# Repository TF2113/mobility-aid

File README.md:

<h1 align="center">Huia Echo 🐸</h1>

# 👁️‍🗨️ Mobility Aid for Visually Impaired Users

A low-cost embedded system designed to assist visually impaired individuals using real-time **proximity sensing** and **traffic light recognition**. Built on a Raspberry Pi, the system integrates ultrasonic sensors, a camera, and a lightweight machine learning model (YOLOv11n) to detect environmental conditions and provide haptic feedback.

---

## 📌 Overview

This mobility aid project helps users safely navigate streets, particularly at pedestrian crossings. The system combines:

- **Ultrasonic sensing** to detect nearby obstacles
- **Traffic light recognition** using a camera and an efficient YOLOv11n model
- **Feedback mechanism** via vibration, triggered based on proximity and light state

---

## 📁 Key File Structure

```
mobility-aid/
│
├── include/                  # C header files
│   ├── config_loader.h       # Loads external config values
│   ├── gpio_functions.h      # GPIO pin setup and control
│   └── tick.h                # Timing utilities
│
├── src/                      # C source files
│   ├── configs/              # Config database using data generated by web app
│   │   └── config.db
│   └── sys_controller.c      # Ultrasonic sensor and control loop                         
│
├── ml/                       # Machine learning module
│   ├── augmentation.ipynb    # Data augmentation and preprocessing
│   ├── train_model.ipynb     # YOLOv11n training logic
│   └── models/
│       └── best.pt           # Trained YOLOv11n model weights
│
├── test/                     # Test cases, mocks and framework files for testing C & Python
│
├── web/                      # Web interface (Flask app)
│   └── app.py                # Local dashboard
│
├── Makefile                  # Compiles the C code
├── .gitignore
├── start.py                  # Orchestrates all components (C binary, ML, server)    
├── requirements.txt
└── README.md                 
```

---

## 🚀 Features

- 📡 **Ultrasonic Sensing**  
  Detects objects and measures distance with HC-SR04 sensor.

- 🧠 **Traffic Light Recognition (YOLOv11n)**  
  Recognizes red/green pedestrian and traffic lights from a camera feed.

- 🔊 **Feedback System**  
  Triggers vibration when objects are too close or crossing is unsafe.

- ⚙️ **Modular Design**  
  Split into embedded C for performance and Python for AI tasks.

- 🪛 **Easily Configurable**  
  Adjust logic thresholds via external config files.

---

## 🧠 Machine Learning

- **Model:** YOLOv11n (Ultralytics)
- **Dataset:** Custom images gathered and augmented to increase dataset size
- **Use Case:** Detect green/red pedestrian signals in real time
- **Output:** Torch `.pt` model located at `ml/models/best.pt`
- **Trained Using:**  
  - `augmentation.ipynb`: Image resizing, color shifts, flips  
  - `train_model.ipynb`: Fine-tuning YOLOv11n with labeled traffic light data

## 🖥️ Requirements

### Hardware

- Raspberry Pi 4 (or newer)
- HC-SR04 Ultrasonic sensor
- Pi Camera Module
- Vibration motor or buzzer

---

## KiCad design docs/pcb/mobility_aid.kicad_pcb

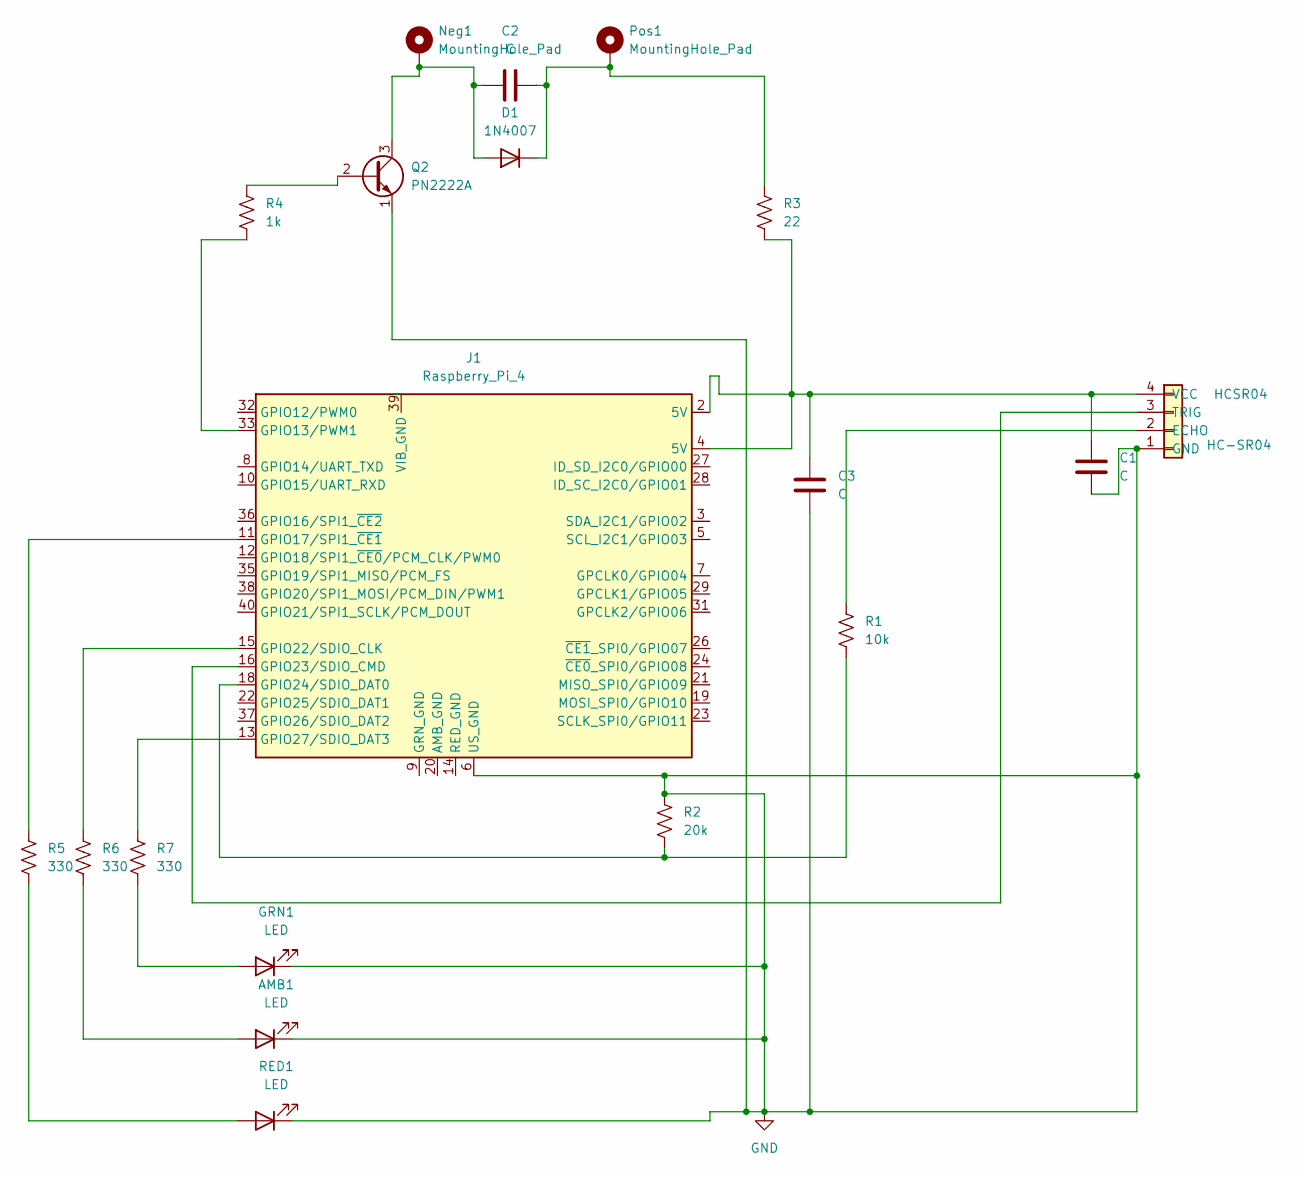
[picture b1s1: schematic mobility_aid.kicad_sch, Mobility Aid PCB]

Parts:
AMB1: LED; LED_D5.0mm
C1, C2: C; C_Disc_D5.0mm_W2.5mm_P2.50mm
C3: C; CP_Radial_D6.3mm_P2.50mm
D1: 1N4007; D_DO-41_SOD81_P10.16mm_Horizontal
GRN1: LED; LED_D5.0mm
HCSR04: HC-SR04; PinSocket_1x04_P2.54mm_Horizontal
J1: Raspberry_Pi_4; PinSocket_2x20_P2.54mm_Vertical
Neg1: MountingHole_Pad; MountingHole_2.5mm_Pad
Pos1: MountingHole_Pad; MountingHole_2.5mm_Pad
Q2: PN2222A; TO-92_Inline
R1: 10k; R_Axial_DIN0207_L6.3mm_D2.5mm_P7.62mm_Horizontal
R2: 20k; R_Axial_DIN0207_L6.3mm_D2.5mm_P7.62mm_Horizontal
R3: 22; R_Axial_DIN0207_L6.3mm_D2.5mm_P7.62mm_Horizontal
R4: 1k; R_Axial_DIN0207_L6.3mm_D2.5mm_P7.62mm_Horizontal
R5, R6, R7: 330; R_Axial_DIN0207_L6.3mm_D2.5mm_P7.62mm_Horizontal
RED1: LED; LED_D5.0mm

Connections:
GND: AMB1.1 (K), C1.2, C3.2, GRN1.1 (K), HCSR04.1 (GND), J1.6 (US_GND), J1.9 (GND), J1.14 (GND), J1.20 (GND), J1.25 (GND), J1.30 (GND), J1.34 (GND), J1.39 (GND), Q2.1 (E), R2.1, RED1.1 (K)
unnamed: AMB1.2 (A), R6.2
unnamed: C2.1, D1.2 (A), Neg1.1, Q2.3 (C)
unnamed: C2.2, D1.1 (K), Pos1.1, R3.1
unnamed: GRN1.2 (A), R7.2
unnamed: HCSR04.2 (ECHO), R1.1
unnamed: HCSR04.3 (TRIG), J1.16 (GPIO23/SDIO_CMD)
unnamed: C1.1, C3.1, HCSR04.4 (VCC), J1.2 (5V), J1.4 (5V), R3.2
unnamed: J1.33 (GPIO13/PWM1), R4.2
unnamed: J1.11 (GPIO17/SPI1_~CE1), R5.1
unnamed: J1.15 (GPIO22/SDIO_CLK), R6.1
unnamed: J1.18 (GPIO24/SDIO_DAT0), R1.2, R2.2
unnamed: J1.13 (GPIO27/SDIO_DAT3), R7.1
unnamed: Q2.2 (B), R4.1
unnamed: R5.2, RED1.2 (A)

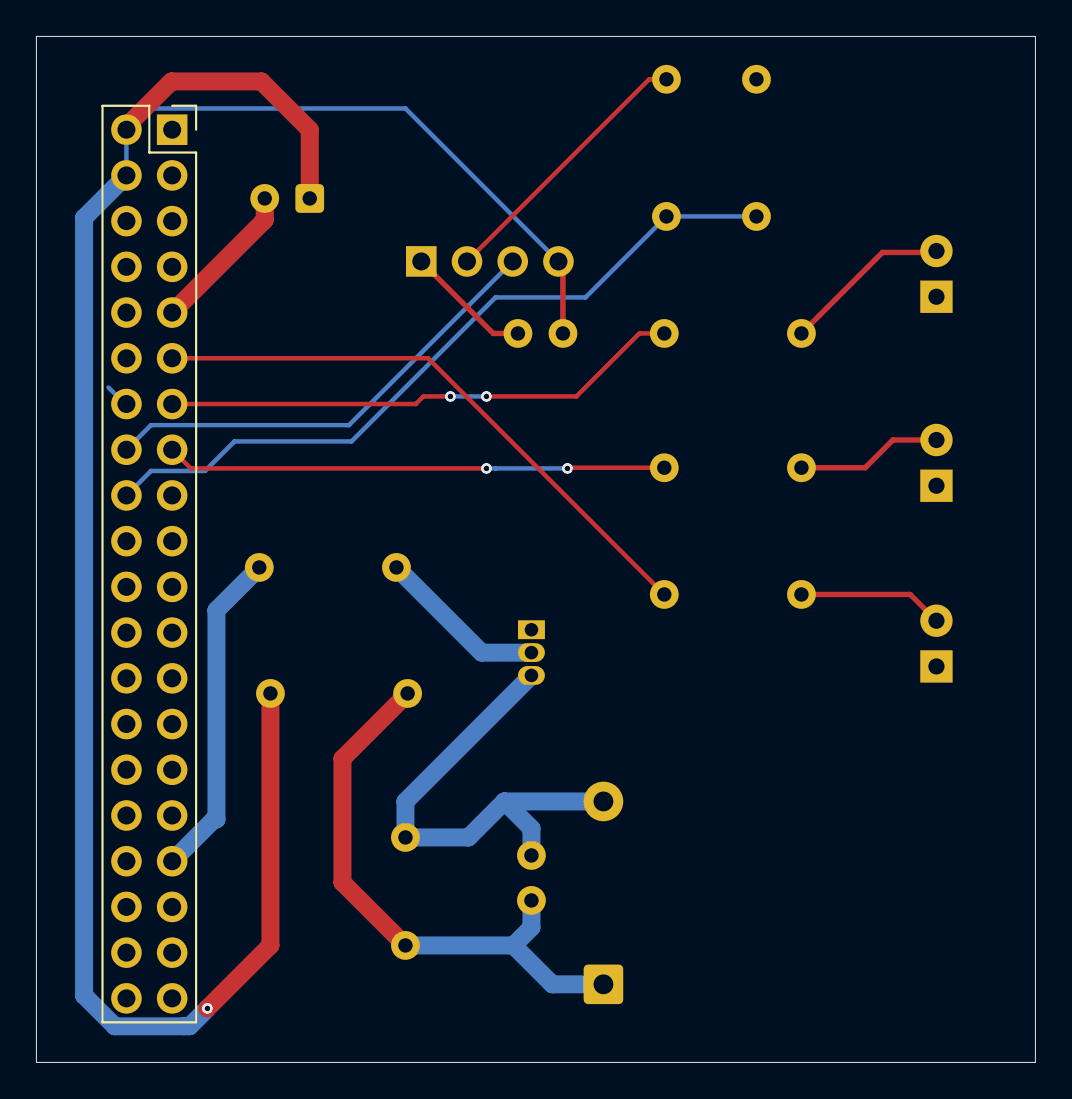
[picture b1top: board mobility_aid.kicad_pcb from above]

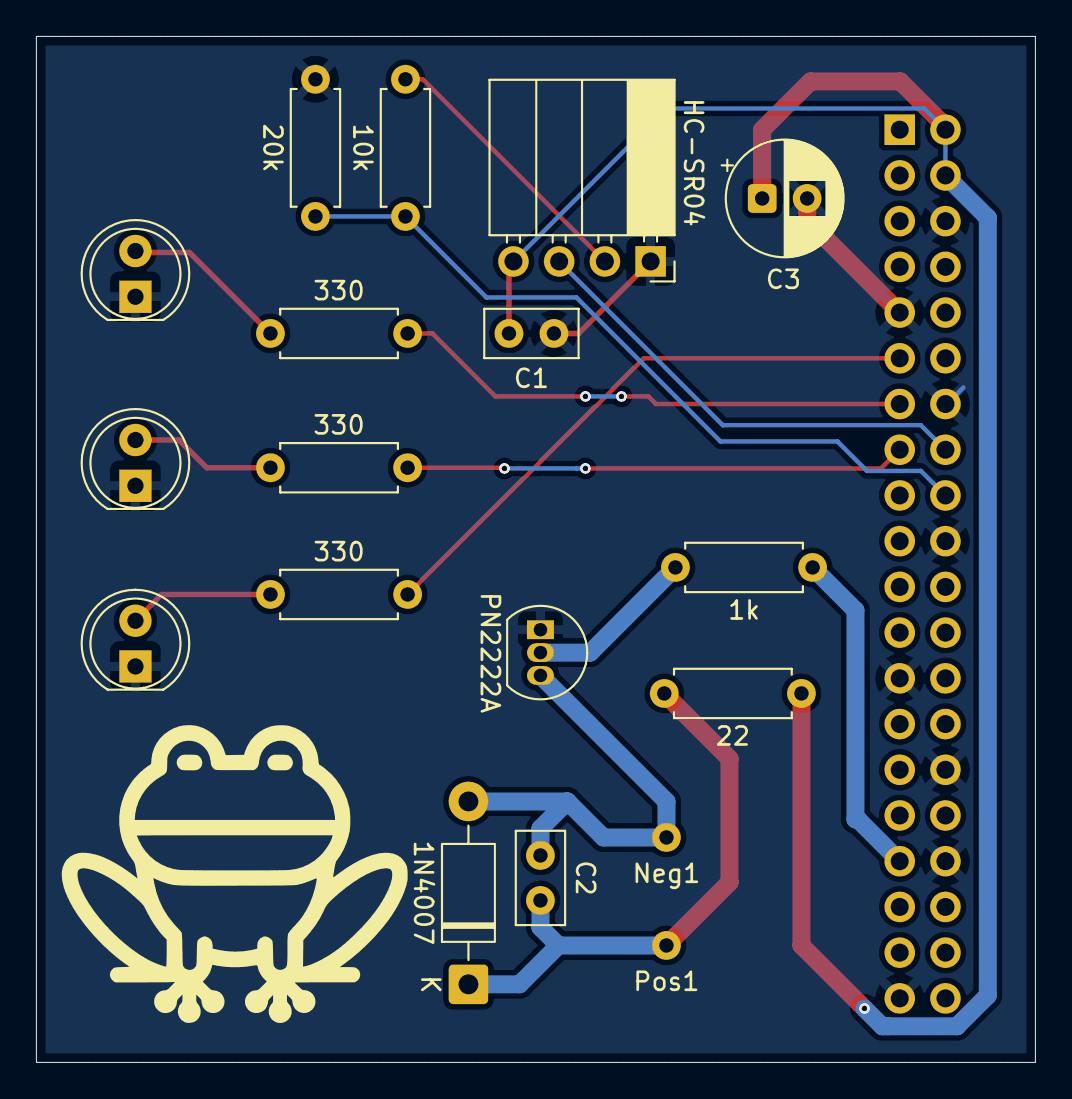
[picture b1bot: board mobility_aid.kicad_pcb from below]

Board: 2 copper layers, 55.5 x 57.0 mm, 19 parts (18 on the bottom side), 15 nets.

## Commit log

2025-06-09 Add initial implementation of GPIO memory access
2025-06-09 Initialize GPIO registers for TRIG, ECHO, and LED in proximity sensor setup
2025-06-09 Add getTick utility functions and update .vscode configuration files
2025-06-09 Update C/C++ configuration for ARM64 support and clean up include paths
2025-06-10 Rename header and struct to avoid <time.h> conflicts, implement distance sensing with LED response
2025-06-10 Add further comments to clarify code
2025-06-10 Compile basic program
2025-06-10 Add Makefile for compiling to /builds, remove git tracking for /builds
2025-06-10 Update comments
2025-06-10 Add green power indicator LED that is on while program is running
2025-06-10 Add loop to blink LED when proximity detected and print distance measured
2025-06-10 Add distance-based blinking frequency for LED
2025-06-11 Create C++ program to capture image from R Pi Camera
2025-06-11 Fix indentation
2025-06-11 Update Makefile to include both current programs
2025-06-13 Add yellow LED for intermediate distance added, refactor GPSEL2 logic to modify all related GPIO at once, code formatted
2025-06-13 Fix commit error
2025-06-13 Remove delay after red GPCLR for faster feedback before next reading
2025-06-16 Add GPIO functions to external .c file to improve modularity
2025-06-16 Refactor prox_sensor to use new GPIO functions module, fix syntax bug in gpioLevel0 function
2025-06-16 Remove redundant definitions
2025-06-16 Move datasheet link from prox_sensor to gpio_functions.c
2025-06-19 Create first iteration of image augmentation pipeline using Albumentations
2025-06-19 Remove image zip output
2025-06-20 Move augmentations.ipynb to ML folder
2025-06-20 Move ML folder out of src folder
2025-06-20 Remove unused import
2025-07-02 Create intial model training notebook
2025-07-02 Update output file structure to work better for training
2025-07-02 Add classes.txt file to output zip
2025-07-02 Add augmentation zip file output handling
2025-07-02 Add ML training command to allow for test trainings
2025-07-03 Add vibration feedback functionality for object proximity
2025-07-03 Update previous comments to reflect new logic
2025-07-10 Add trained model converted to NCNN format
2025-07-10 Add conversion to NCNN format after training
2025-07-10 Change ml directory structure
2025-07-10 Update Makefile for system wide NCNN install
2025-07-10 Initial inference program
2025-07-10 Remove unused directories from .gitgnore
2025-07-10 Add test inference program using Pytorch model and Python
2025-07-11 Refactor program to use Python for inference
2025-07-11 Add automatic image capture and inference program
2025-07-11 Remove conversion to NCNN format from training process
2025-07-11 Change image capture from libcamera to rpicam, remove camera logs from console output
2025-07-11 Add simple vibrate when certain label is detected
2025-07-14 Implement first version configuration dashboard for proximity settings and camera control
2025-07-16 Remove .vscode config files from git tracking
2025-07-16 Remove .vscode configuration files from git tracking
2025-07-16 Implement writing to config file from web app route
2025-07-16 Remove tracking from pycache
2025-07-16 Add helper function to load and read config files
2025-07-16 Remove configs from git tracking
2025-07-16 Add config_loader.c to build process in Makefile
2025-07-16 Fix small syntax errors in Makefile and config_loader
2025-07-16 Add file close to end of function
2025-07-16 Refactor proximity sensor logic to use configurable distance thresholds and load configuration at startup
2025-07-16 Fix target name in Makefile to use underscores instead of hyphens
2025-07-16 Refactor main loop to super loop with interrupting logic
2025-07-16 Add comment for SIGTERM in prox_sensor.c
2025-07-16 Add initial implementation of start script to launch mobility aid
2025-07-16 Rename capture_image.py to inference.py better describe functionality
2025-07-16 Add server and inference process management to start script
2025-07-16 Remove capture_image.py as functionality is now handled by inference.py
2025-07-17 Refactor styles and update SVG for improved UI consistency
2025-07-17 Enhance config loading by monitoring file changes and reloading on update
2025-07-17 Update form labels for clarity in configuration settings
2025-07-17 Update log to print measurement before feedback
2025-07-17 Add camera toggle functionality to web app and config update checker
2025-07-17 Add image deletion process when camera feed is turned off or program stops
2025-07-17 Add responsive mobile scaling to web page
2025-07-17 Rename project
2025-07-18 Update comments to reflect updatable variables
2025-07-18 Allow for listening across network
2025-07-24 Initial database setup
2025-07-24 Update startup to create db
2025-07-24 Remove files relating to config.txt
2025-07-24 Update web app to use SQLite for storing config data
2025-07-24 Addd python init files for importing local functions
2025-07-24 Define helper functions for C SQL implemetation
2025-07-24 Update main prox_sensor program to check for updates from DB
2025-07-29 Refactor vibrate.c to allow for defining vibration patterns
2025-07-29 Update vibrate call to define patterns for difference pedestrian crossings
2025-07-29 Fix bug causing infinite vibration due to conflicting vibrate calls from inference.py and prox_sensor.c
2025-07-29 Fix bug causing prox_sensor to be skipped due to timing errors by adding queue for inference vibration
2025-07-29 Add max size to queue to prevent outdated information being executed upon
2025-07-29 Refactor prox_sensor.c to use vibrate.c for vibration instead of unique implementation
2025-07-29 Add timeout to sensor readings to prevent hangs
2025-07-29 Add file lock to vibrate.c to prevent multiple concurrent calls
2025-07-29 Replace blocking system(cmd) calls with fork and execute for non-blocking vibrate calls
2025-07-29 Add Python requirements.txt
2025-07-30 Assign seperate CPU cores to C programs and Python scripts to prevent interference
2025-07-30 Create header file for vibrate.c and refactor main to allow for external testing of CLI function
2025-07-30 Add Unity testing framework to .gitignore
2025-07-30 Create skeleton for vibrate.c testing
2025-07-30 Initial unit test for invalid num args
2025-07-30 Create mock vibrate.c cli interface functions for testing
2025-07-30 Update Makefile for testing compilation and improved readability
2025-07-30 Allow Unity to use doubles
2025-07-30 Add valid args test for cli vibrate
2025-07-30 Add header file for vibrate_mock testing
2025-07-30 Add counter to mock functions to mimic real calls following GPIO calls in vibrate.c
2025-07-31 Update Makefiile for new test file
2025-07-31 Setup GPIO mock test functions
2025-07-31 Rename file for better clarity of purpose
2025-07-31 Rename enum value for accuracy to function
2025-07-31 Implement mock functions for functions used in vibrate.c
2025-07-31 Add safe removal of output file should test case stop early
2025-07-31 Move mock files to new mock folder
2025-07-31 Fix compile errors from incorrect returns and unused args
2025-07-31 Update Makefile to reflect new mock folder and main test runner file
2025-07-31 Remove main, set up and tear down to centralise test running
2025-07-31 Remove set up and tear down from individual file
2025-07-31 Create test_runner.c to run all setup, testing and tear down from one file
2025-07-31 Separate testing for logic and abstracted CLI functions
2025-07-31 Update Makefile to reflect file changes
2025-07-31 Create new version of vibrate.c without main for testing logic
2025-07-31 Add testing includes
2025-07-31 Move vibrate_unit.c to mocks folder
2025-08-01 Add test for negative values passed
2025-08-01 Add correct validation of cli_vibrate types before executing
2025-08-01 Add tests for validating correct data type in CLI args
2025-08-01 Define macro to remove repeated test setup code
2025-08-01 Add test for no args passed to cli_vibrate
2025-08-01 Update comments to clarify error
2025-08-01 Add tests for mock file opening logic
2025-08-01 Fix incorrect test logic to test vibrate_unit.c logic instead of open() directly
2025-08-01 Add additional I/O negative testing
2025-08-05 FIx mismatched test names
2025-08-05 Initial DB configuration Unity test cases
2025-08-05 Update makefile for new DB test runner
2025-08-05 Add tests for various values being passed to the SQL statement
2025-08-05 Rename prox_sensor.c to sys_controller.c to better reflect purpose
2025-08-05 Implement positive path tests for gpio_functions.c
2025-08-05 Update Makefile for gpio test runner
2025-08-05 Add unit tests for GPIO functions
2025-08-05 Add test-run to Makefile for executing updated test runners
2025-08-06 Refactor of sys_controller.c to seperate functionality to individual files
2025-08-06 Header files for new function files
2025-08-06 Refactor of vibrate.c to remove repeated code & improve readability
2025-08-06 Updated Makefile for new .c and .h files
2025-08-06 Fix formatting due to updated Makefile
2025-08-06 Move test runners into seperate directory
2025-08-06 Update Makefile sources for test/runners/
2025-08-07 Update ultra_sensor for proper test capabilties
2025-08-07 Implement test runner for ultra_sensor.c
2025-08-07 Add test functions for ultra_sensor.c
2025-08-07 Update Makefile for new test runner
2025-08-07 Further CPU priority optimizations to help prevent race conditions
2025-08-07 Refactor of app.py for an application factory process
2025-08-07 Add new start point for web app
2025-08-11 Initial web app test cases & config using PyTest
2025-08-11 Update .gitignore for python config and cache files
2025-08-11 Add test case for empty DB and correct assert params for unchecked camera
2025-08-11 Add additional edge case and error testing cases
2025-08-11 Create Python script to run test programs
2025-08-11 Update requirements.txt with new packages
2025-08-11 Add main loop in start.py to run() function
2025-08-11 Add additional pycache folders to ,gitignore
2025-08-11 Implement test cases for start.py
2025-08-13 Upload wiring diagrams used for hardware
2025-08-13 Implement initial test cases for db.py
2025-08-13 Update comments and formatting
2025-08-13 Create pytest.ini to define custom test markers
2025-08-13 Update .gitignore for pycache
2025-08-13 Update db.py to use global db path
2025-08-13 Implement App to DB integration test
2025-08-13 Update .gitignore to remove src/__pycache__
2025-08-13 Update sys_logic to take db_path as an argument for testability
2025-08-13 Update sys_controller main to take db path as argument for testability
2025-08-13 Update system_init arg mismatch error
2025-08-13 Implement mock version of tick.c for testing
2025-08-13 Update Makefile for new test executable for mobility-aid
2025-08-13 Add running boolean to sys_logic.h for external use
2025-08-13 Update feedback.c to implement more responsive sleep function
2025-08-13 Implement C to DB integration test
2025-08-14 Implement E2E test for testing web app changes affect the hardware
2025-08-14 Update e2e test to use global env for test specific executable
2025-08-14 Update start.py to use testable env executable when appropriate
2025-08-15 Upload short clips for testing ML model
2025-08-15 Create testing cli script for ML model
2025-08-15 Upload example output logs files from test_ml.py
2025-08-15 Upload credits for video clips used
2025-08-15 Update name to avoid pytest auto run
2025-08-15 Update to .gitignore to ignore all __pycache__ folders
2025-09-03 Upload PCB files to repo
